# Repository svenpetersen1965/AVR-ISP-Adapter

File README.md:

# AVR-ISP-Adapter
The ISP (in system programming) connector for Atmel µControllers is not compatible for breadboards. This is an adater, which allows to connect a 2x3 pin programmer connector to the projects.

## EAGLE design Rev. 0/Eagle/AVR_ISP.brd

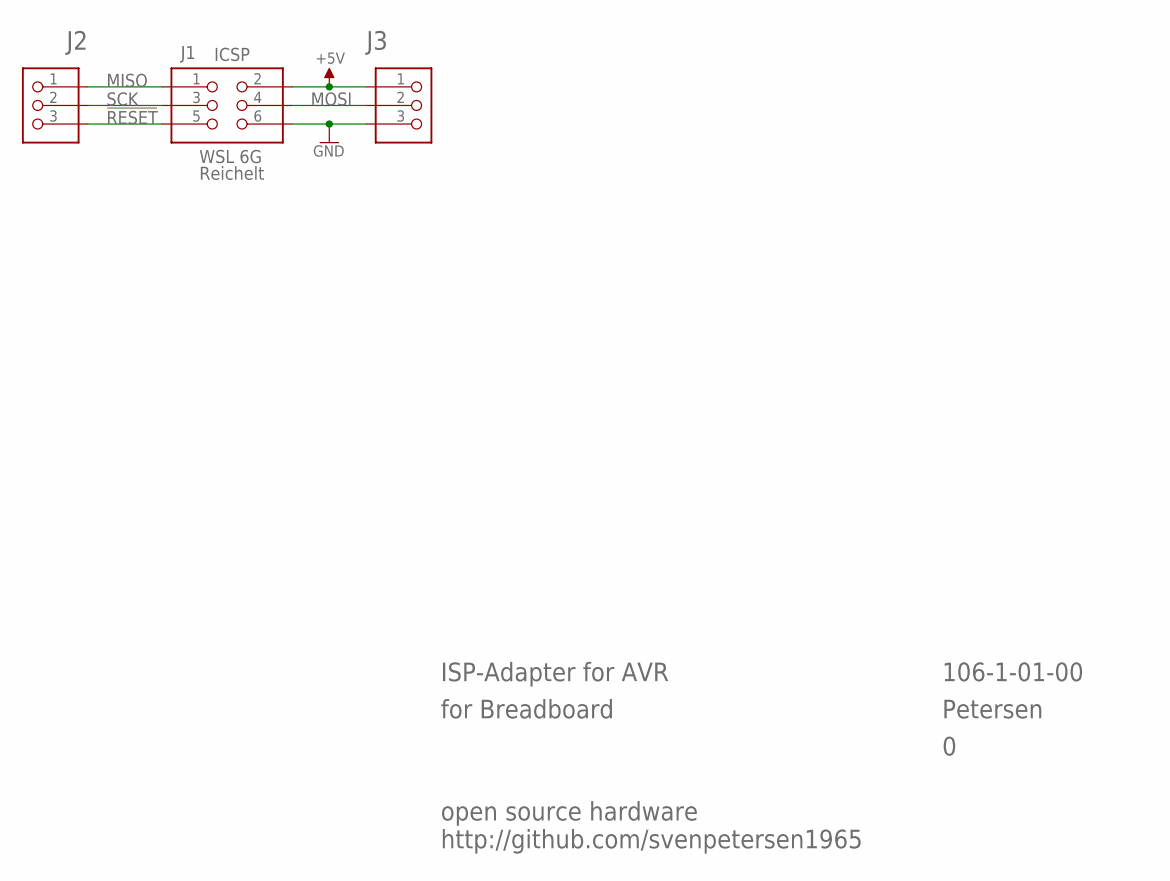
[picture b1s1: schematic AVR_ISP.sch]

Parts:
J1: WSL 6G; 2X03WV
J2, J3: PINHD-1X3; 1X03

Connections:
!RESET: J1.5, J2.3
+5V: J1.2, J3.1
GND: J1.6, J3.3
MISO: J1.1, J2.1
MOSI: J1.4, J3.2
SCK: J1.3, J2.2

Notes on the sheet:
ICSP
Reichelt
ISP-Adapter for AVR
for Breadboard
Petersen
106-1-01-00
http://github.com/svenpetersen1965
open source hardware

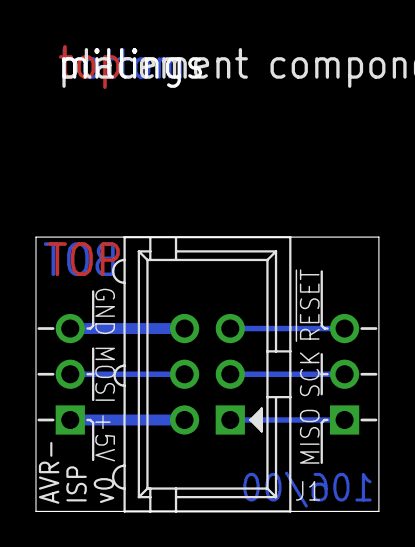
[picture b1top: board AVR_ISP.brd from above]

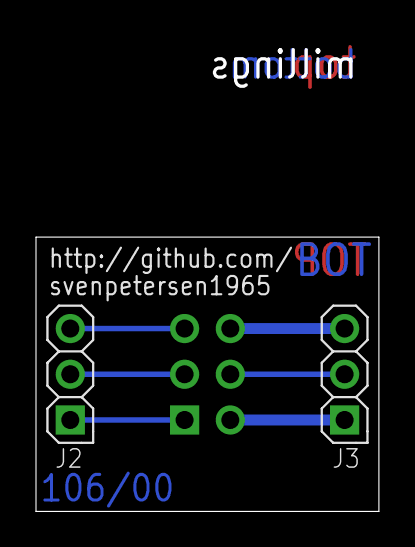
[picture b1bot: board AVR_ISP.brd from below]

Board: 2 copper layers, 19.1 x 15.2 mm, 5 parts (2 on the bottom side), 6 nets.

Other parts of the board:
U$2: PCB-TITLE/
U$5: 2LAYER

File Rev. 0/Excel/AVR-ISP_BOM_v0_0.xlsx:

AVR-ISP Adapter Rev. 0
Bill of Material Rev. 0.0
Pos. | Qty | Value | Footprint | Ref.-No. | Comment
1 | 1 | 106-2-01-00 | 2 Layer | PCB Rev. 0 | 2 layer, Cu 35µ, HASL, 19.1mm x 15.2mm, 1.6mm FR4
2 | 1 | WSL 6G | 2X03WV | J1 | box pin header, 2x3pin, 2.54mm pitch
3 | 2 | 1x3 | 1X03 | J2, J3 | pin header 1x3pin, 2.54mm pitch
